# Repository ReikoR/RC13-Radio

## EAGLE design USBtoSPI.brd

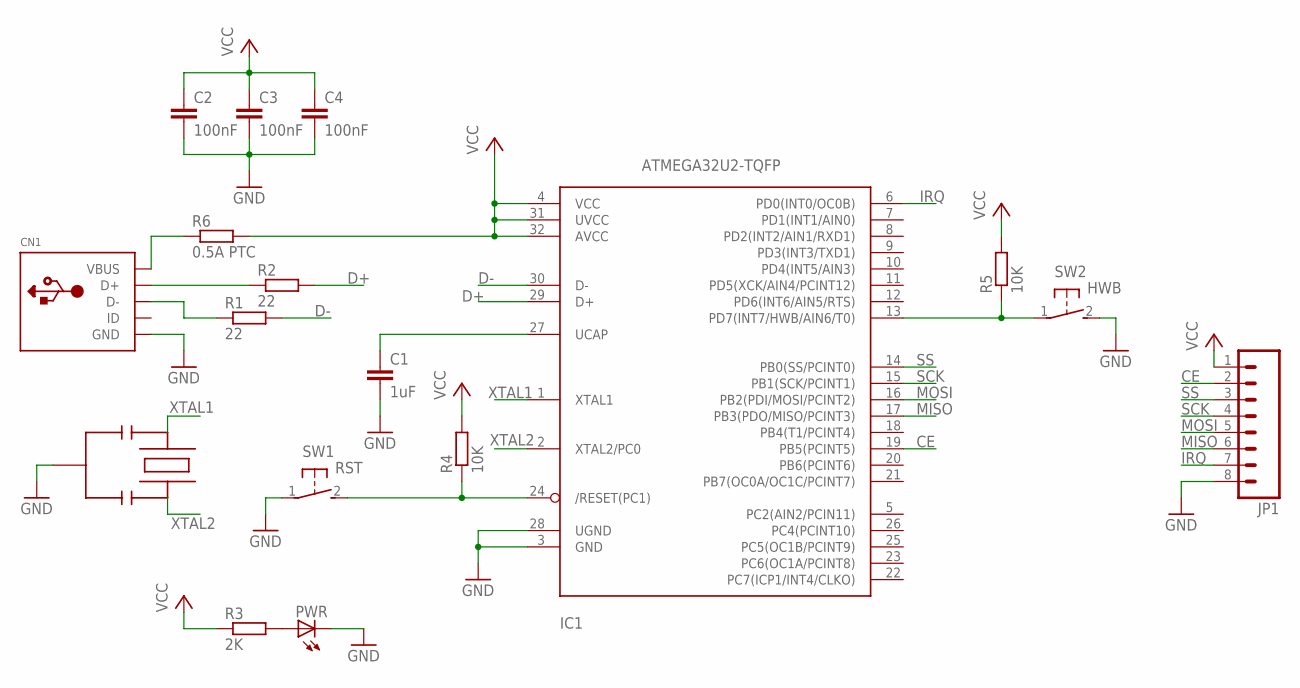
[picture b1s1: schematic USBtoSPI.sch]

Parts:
C1: 1uF; C0603
C2, C3, C4: 100nF; C0603
CN1: USBMINIB; USB-MINIB
IC1: ATMEGA32U2-TQFP; TQFP32-08
JP1: M081X08; 1X08
PWR: LEDCHIP-LED0603; CHIP-LED0603
R1, R2: 22; R0603
R3: 2K; R0603
R4, R5: 10K; R0603
R6: 0.5A PTC; R1210
SW1: RST; SMD-TACT-3.9X2.9
SW2: HWB; SMD-TACT-3.9X2.9
U$1: SMDRESONATORPBRC-H; SMDRESONATOR

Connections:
CE: IC1.19 (PB5(PCINT5)), JP1.2
D+: IC1.29 (D+), R2.2
D-: IC1.30 (D-), R1.2
GND: C1.2, C2.2, C3.2, C4.2, CN1.GND, IC1.3 (GND), IC1.28 (UGND), JP1.8, PWR.C, SW1.1, SW2.2, U$1.P$1
IRQ: IC1.6 (PD0(INT0/OC0B)), JP1.7
MISO: IC1.17 (PB3(PDO/MISO/PCINT3)), JP1.6
MOSI: IC1.16 (PB2(PDI/MOSI/PCINT2)), JP1.5
unnamed: CN1.D-, R1.1
unnamed: CN1.D+, R2.1
unnamed: C1.1, IC1.27 (UCAP)
unnamed: IC1.24 (/RESET(PC1)), R4.1, SW1.2
unnamed: IC1.13 (PD7(INT7/HWB/AIN6/T0)), R5.1, SW2.1
unnamed: PWR.A, R3.2
unnamed: CN1.VBUS, R6.1
SCK: IC1.15 (PB1(SCK/PCINT1)), JP1.4
SS: IC1.14 (PB0(SS/PCINT0)), JP1.3
VCC: C2.1, C3.1, C4.1, IC1.4 (VCC), IC1.31 (UVCC), IC1.32 (AVCC), JP1.1, R3.1, R4.2, R5.2, R6.2
XTAL1: IC1.1 (XTAL1), U$1.P$2
XTAL2: IC1.2 (XTAL2/PC0), U$1.P$3

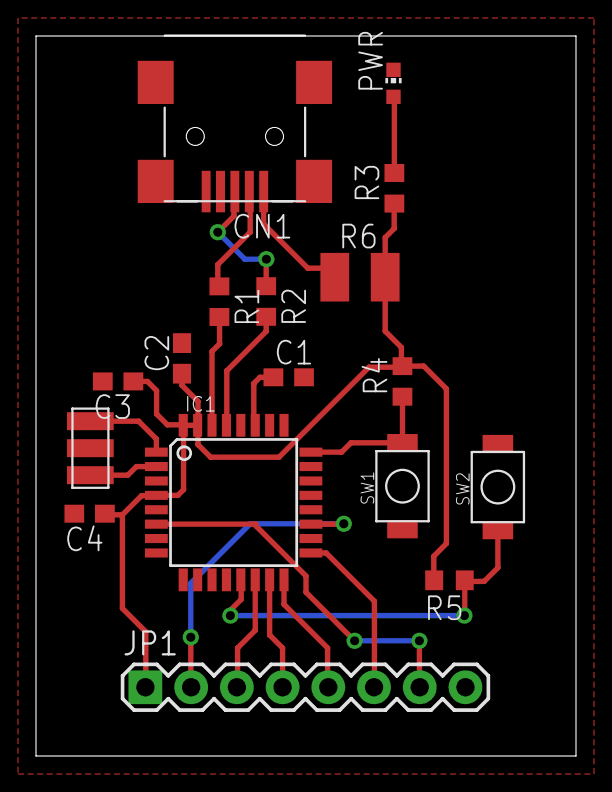
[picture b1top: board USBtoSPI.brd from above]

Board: 2 copper layers, 30.0 x 40.0 mm, 17 parts (0 on the bottom side), 19 nets.

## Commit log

2013-06-18 Added existing Eagle files

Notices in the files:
parts and their libraries:
SparkFun-Connectors: Licensing: CC v3.0 Share-Alike You are welcome to use this library for commercial purposes.
